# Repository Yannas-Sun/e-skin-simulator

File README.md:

# Modular e-Skin Network Simulator

This project is a lightweight software simulator for exploring scalable electronics in a modular, multi-layer electronic skin system. It is based on the planning work in `E_skin_plan_report.pdf`, which studies how an existing multi-modal e-skin platform can be redesigned into a compact, modular architecture with better data, power, and calibration scalability.

## Background

The simulated e-skin module follows the hardware structure described in the report:

- Hexagonal honeycomb-style module geometry
- Two internal `16 x 16` FSR force-sensing layers
- One `4 x 4` LIS3DH accelerometer layer
- Module-level sensing with patch-level aggregation
- Data throughput estimated from `560 channels/module` at a configurable sampling rate

The simulator is intended as an early design and communication tool rather than a high-fidelity finite-element or electronics model.

## Hardware Module Preview

The simulator is developed alongside a modular hardware prototype. Each hexagonal module is designed as a compact stack containing a local mainboard, a distributed accelerometer layer, and a folded FSR pressure-sensing array.

The same geometry supports patch-level assembly. The render below shows a five-module configuration that motivates the simulator's honeycomb workspace, patch grouping, and scalable data-throughput tools.

The complete PCB layouts, schematics, layer renders, and hardware development notes are maintained on the [`codex/hardware-prototype` branch](https://github.com/Yannas-Sun/e-skin-simulator/tree/codex/hardware-prototype).

## Embedded Firmware

The `firmware/` directory contains the current STM32G474 and Teensy 4.1 source,
Windows build/flash launchers, combined and standalone PC GUIs, and hardware
isolation tests for the physical module. The implemented prototype acquires two
16 x 16 FSR matrices and nine installed LIS2DH12 accelerometers. Start with
[`firmware/README.md`](firmware/README.md) for the current hardware status and
one-command programming workflow.

## Development Status

This project is still under active development. The current repository captures the first programmable simulation workflow, hardware-readout demo, and visualization interface. New functions will continue to be added, including richer scan strategies, external MCU-in-the-loop testing, event-driven sensing experiments, encoder/VAE-style data compression, and more complete multi-patch communication models.

## Features

### Module Network Dashboard

- Drag hexagonal e-skin modules into a honeycomb grid
- Assemble modules into arbitrary edge-aligned networks
- Box-select multiple modules or test objects
- Move, copy, paste, and delete selected items
- Combine selected modules into a patch
- Click a patch label or outline to focus the workspace view on that patch
- Show heatmap and throughput data for the focused patch until another item is selected
- Drag test objects onto the module network
- Choose object shape: circle, square, or triangle
- Adjust object size and mass
- Zoom the workspace using the mouse wheel, centered on the cursor
- Display a live pressure heatmap matching the assembled module topology
- Show module IDs on the heatmap
- Estimate real-time data throughput and Ethernet link use

### Programmable FSR Readout Demo

- Open an FSR readout demo showing DMUX row selection, 16 x 16 FSR voltage-divider readout, 16-channel ADC sampling, and four-wire SPI transfer back to the MCU
- Run the FSR demo from programmable Python virtual hardware classes rather than frontend-only formulas
- Simulate a MAX11632-style ADC command flow, including setup, averaging, reset, conversion input bytes, FIFO readout, EOC behavior, and 16-bit MISO output words
- Enter custom MOSI byte sequences from the web UI and inspect the resulting MISO FIFO output
- Generate the FSR heatmap from scanned ADC/FIFO data rather than directly from object placement
- Switch visualization behavior by refresh rate while keeping the same scan pipeline: MUX row scan followed by ADC FIFO column output
- Use the simulator as a bridge toward physical MCU testing, where an external MCU can later drive or validate the same command and data-transfer logic

### Programmable LIS3DH Accelerometer Demo

- Open an accelerometer demo showing a 4 x 4 LIS3DH array with shared SPI and individual chip-select control through a MUX
- Simulate LIS3DH SPI command encoding: `R/W`, multi-byte auto-increment, and 6-bit register address
- Read `OUT_X_L` through `OUT_Z_H` using the datasheet-style `0xE8` command byte
- Adjust the virtual object's vibration strength and footprint
- Decode X/Y/Z acceleration only from returned MISO register bytes
- Generate the hardware heatmap from decoded MISO data rather than direct object placement
- Display counted SPI traffic for address lines, SCK, MOSI, MISO, CS, and the upstream MCU-to-FPGA frame
- Solve the active-low LIS3DH chip-select electrical layer through ngspice when the solver is available

## Demo Videos

The repository includes two embedded demo previews to document the current simulator behavior. The original MP4 recordings are kept in `docs/demo/`, while the GIF previews below are used because GitHub README pages do not render repository-hosted MP4 files as inline players.

### Programmable FSR Readout Demo

Demonstrates the programmable FSR readout page, including MUX-controlled row scanning, ADC/FIFO-based column readout, MOSI command input, MISO output inspection, and hardware-derived heatmap generation.

### Module Network Dashboard

Demonstrates the modular e-skin dashboard, including honeycomb-style module placement, object interaction, patch-oriented pressure visualization, module identifiers, and data-throughput feedback.

These videos show the current state of the prototype. The simulator remains in progress, and future videos will be updated as new hardware models, external MCU workflows, scan strategies, and algorithm experiments are added.

## Running

This project uses only the Python standard library for the backend and plain HTML/CSS/JavaScript for the frontend.

```powershell
python server.py
```

Then open:

```text
http://127.0.0.1:8000
```

Use the HTTP address above rather than opening `index.html` directly, because the frontend calls the Python backend API at `/api/simulate`.

## ngspice Electrical Backend

The project includes an optional ngspice adapter for circuit-level simulation. The current deployment uses the official Windows 64-bit ngspice console executable and keeps the downloaded runtime under the ignored local `tools/ngspice/` directory.

The backend discovers ngspice in this order:

1. `NGSPICE_EXECUTABLE`
2. `tools/ngspice/Spice64/bin/ngspice_con.exe`
3. `ngspice_con` or `ngspice` on `PATH`

The health endpoint runs a `3.3 V` FSR voltage-divider smoke test through ngspice:

```text
http://127.0.0.1:8000/api/ngspice-health
```

The interactive FSR demo now uses ngspice for the selected-row electrical network. For each scanned row, Python computes the current FSR resistance values, ngspice solves the row source, MUX on-resistance, 16 FSRs, and 16 load resistors, then the Python MAX11632 model converts those node voltages into FIFO and MISO words.

The accelerometer demo uses ngspice for the LIS3DH active-low chip-select electrical layer. The address decoder network is solved as 16 nCS lines with pull-ups, LIS3DH input leakage, and one selected decoder sink. Python then continues with the digital LIS3DH register/SPI behavior. The dashboard-level module heatmap still uses the fast Python pressure model.

## Fusion 3D Model Preview

The dashboard includes a load-on-demand Fusion OBJ preview for the module model. The large `Module.obj` asset is tracked with Git LFS through `.gitattributes`, while the viewer uses a small vendored Three.js subset so the preview works without a CDN.

## Basic Usage

1. Drag an `e-Skin Module` from the right panel into the workspace.
2. Arrange modules on the honeycomb grid.
3. Drag a test object into the workspace.
4. Adjust object size, mass, and sampling rate from the right panel.
5. Read the pressure heatmap and data throughput from the left panel.
6. Drag on empty workspace space to box-select multiple items.
7. Use toolbar buttons or shortcuts:
   - `Copy`
   - `Paste`
   - `Delete`
   - `Ctrl+C`
   - `Ctrl+V`
   - `Delete` / `Backspace`
8. Click `FSR Demo` to inspect the hardware readout path for one 16 x 16 FSR layer.
9. Click `Accel Demo` to inspect the LIS3DH accelerometer-array readout path.

## Project Structure

```text
software-simulation/
  server.py                    # root launcher; keeps `python server.py` working
  backend/
    README.md                  # backend package map and API summary
    server.py                  # Python HTTP server and simulation API
    accel/
      README.md                # LIS3DH hardware model documentation
      hardware.py              # virtual LIS3DH, CS MUX, ngspice nCS drive, and SPI primitives
      sampler.py               # programmable LIS3DH scan controller
    electrical/
      README.md                # shared electrical solver documentation
      ngspice_backend.py       # optional circuit-level ngspice adapter and health check
    fsr/
      README.md                # FSR hardware model documentation
      hardware.py              # virtual DMUX, ADC, resistor, FSR, and FSR array primitives
      sampler.py               # programmable FSR scan controller
  circuits/
    ngspice/
      accel-cs-mux.cir         # LIS3DH active-low nCS pull-up/decoder-sink reference circuit
      fsr-divider.cir          # standalone FSR voltage-divider smoke-test circuit
      fsr-selected-row.cir     # selected-row FSR network with MUX on-resistance and 16 load dividers
  frontend/
    assets/
      models/                 # Fusion OBJ/MTL module preview assets
    accelerometer-demo.html    # LIS3DH accelerometer-array readout demo
    index.html                 # module-network dashboard
    fsr-demo.html              # FSR readout circuit demo
    styles.css                 # shared UI styling
    vendor/
      three/                   # vendored Three.js modules used by the OBJ viewer
    js/
      app.js                   # dashboard interaction, rendering, and API calls
      accelerometer-demo.js    # LIS3DH visualization and MISO-driven heatmap logic
      fsr-demo.js              # FSR visualization and MISO-driven heatmap logic
      module-3d-viewer.js      # dashboard Fusion OBJ preview viewer
  docs/
    datasheets/                # component datasheets used by the virtual hardware models
    demo/
      demo1.mp4                # dashboard workflow demo
      demo2.mp4                # programmable FSR readout demo
    hardware/                  # module and patch renders used by this README
    references/                # project reports and source PDFs
  firmware/                    # STM32/Teensy firmware, tests, commands, and PC GUIs
  CHANGELOG.md                 # ordered record of pushed changes
```

Local KiCad prototypes and downloaded helper tools can live beside the simulator under `prototype/` and `tools/`. They are intentionally excluded from software pushes so the repository stays focused on the runnable simulation platform.

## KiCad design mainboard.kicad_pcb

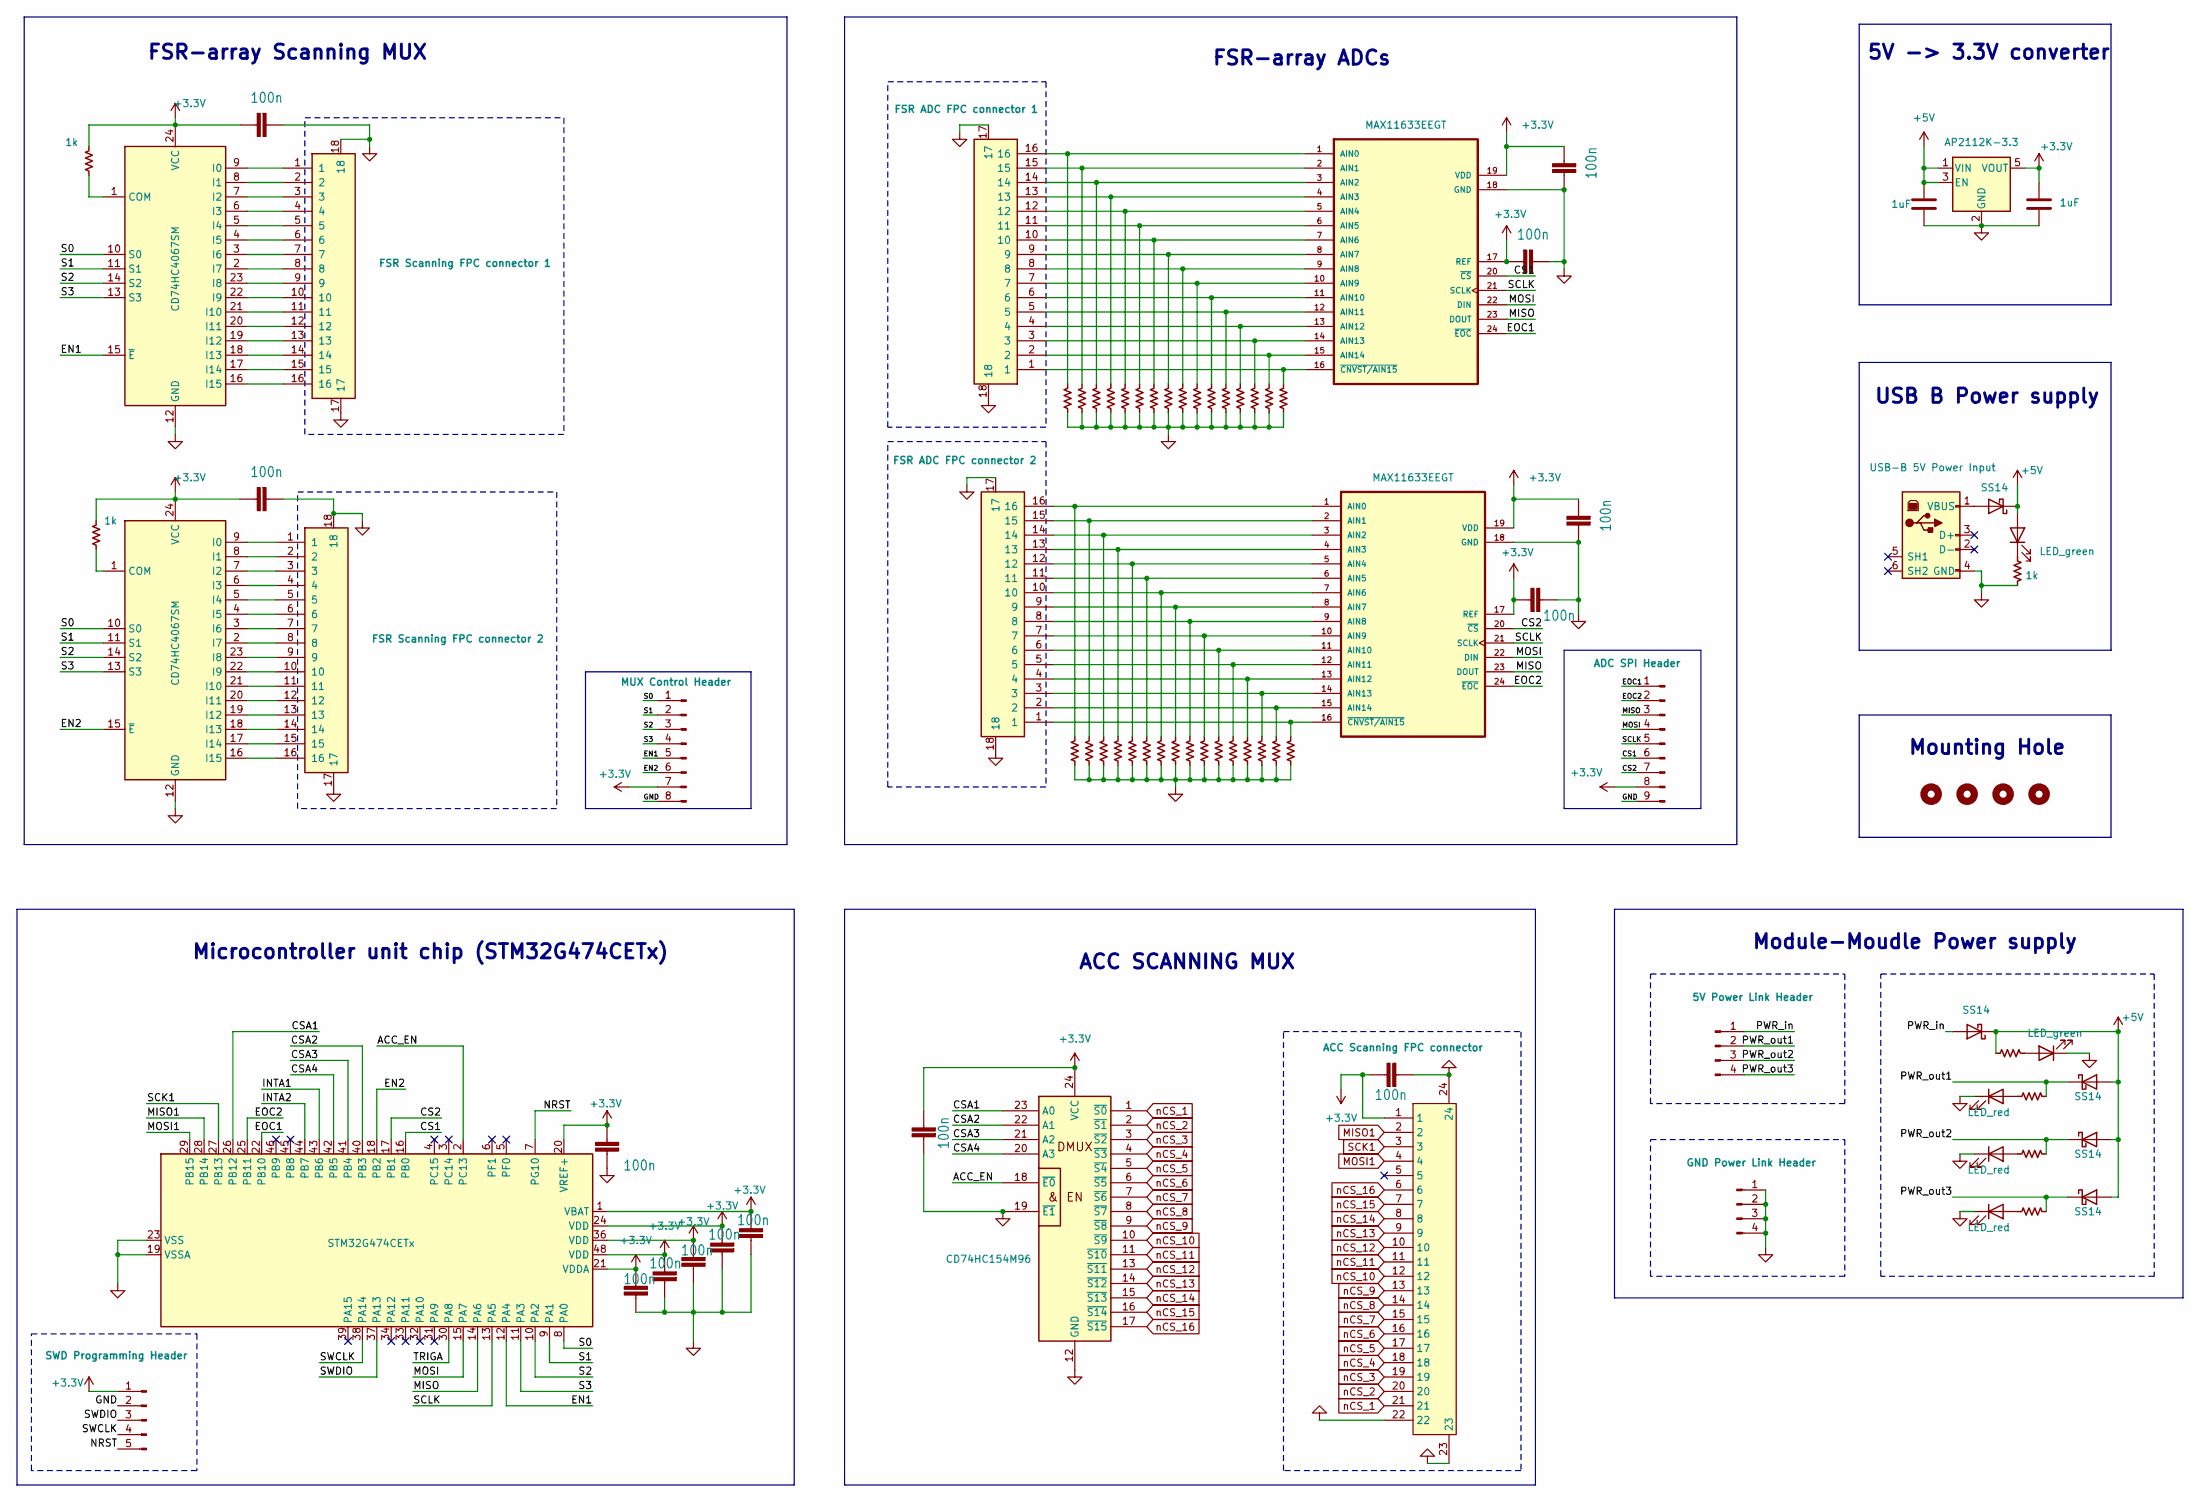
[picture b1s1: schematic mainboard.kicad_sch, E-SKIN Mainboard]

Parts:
ACC_DEC1: CD74HC154M96; SOIC127P1030X265-24N
ACC_FPC1: ACC Scanning FPC connector; AFC01-S22FCA-00; LCSC Part C262668
ADC_SPI_HDR1: ADC SPI Header; PinHeader_1x09_P2.54mm_Vertical
C1, C2, C5, C6, C7, C8, C9, C10, C11, C12, C13, C14, C15, C16: 100n; C0603
C3, C4: 1uF; C0603
COL_ADC1, COL_ADC2: MAX11633EEGT
COL_FPC1: FSR ADC FPC connector 1; AFC01-S16FCA-00
COL_FPC2: FSR ADC FPC connector 2; AFC01-S16FCA-00
D1, D6: LED_green; LED_0603_1608Metric
D2, D3, D4, D5, D10: SS14; D_SMA
D7, D8, D9: LED_red; LED_0603_1608Metric
LDO_3V3: AP2112K-3.3; SOT-23-5
MCU1: STM32G474CETx; LQFP-48_7x7mm_P0.5mm
MOUNT2, MOUNT3, MOUNT4, MOUNT5: M3 Mounting Hole; MountingHole_3.2mm_M3
MUX_CTRL_HDR1: MUX Control Header; PinHeader_1x08_P2.54mm_Vertical
PWR_5V_LINK1: 5V Power Link Header; PinHeader_1x04_P2.54mm_Horizontal
PWR_GND_LINK1: GND Power Link Header; PinHeader_1x04_P2.54mm_Horizontal
ROW_FPC1: FSR Scanning FPC connector 1; AFC01-S16FCA-00
ROW_FPC2: FSR Scanning FPC connector 2; AFC01-S16FCA-00
ROW_MUX1, ROW_MUX2: CD74HC4067SM; SSOP-24_5.3x8.2mm_P0.65mm
R_ADC1_01, R_ADC1_02, R_ADC1_03, R_ADC1_04, R_ADC1_05, R_ADC1_06, R_ADC1_07, R_ADC1_08, R_ADC1_09, R_ADC1_10, R_ADC1_11, R_ADC1_12, R_ADC1_13, R_ADC1_14, R_ADC1_15, R_ADC1_16, R_ADC2_01, R_ADC2_02, R_ADC2_03, R_ADC2_04, R_ADC2_05, R_ADC2_06, R_ADC2_07, R_ADC2_08, R_ADC2_09, R_ADC2_10, R_ADC2_11, R_ADC2_12, R_ADC2_13, R_ADC2_14, R_ADC2_15, R_ADC2_16: 10k; R_0603_1608Metric
R_LED_PWR1, R_LED_PWR2, R_LED_PWR3, R_LED_PWR4: 1k; R_0603_1608Metric
R_LED_USB1: 1k; R_0603_1608Metric
R_MUX1_COM1, R_MUX2_COM1: 1k; R_0603_1608Metric
SWD_HDR1: SWD Programming Header; PinHeader_1x05_P2.54mm_Vertical
USB_PWR_IN1: USB-B 5V Power Input; SS52300001; Mouser Part Number 530-SS-52300-001

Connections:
+3.3V: ACC_DEC1.24 (VCC), ACC_FPC1.1, ADC_SPI_HDR1.8, C1.2, C2.1, C3.1, C5.2, C6.2, C7.2, C8.1, C9.2, C10.2, C11.2, C12.2, C13.2, C14.2, C15.2, C16.2, COL_ADC1.17 (REF), COL_ADC1.19 (VDD), COL_ADC2.17 (REF), COL_ADC2.19 (VDD), LDO_3V3.5 (VOUT), MCU1.1 (VBAT), MCU1.20 (VREF+), MCU1.21 (VDDA), MCU1.24 (VDD), MCU1.36 (VDD), MCU1.48 (VDD), MUX_CTRL_HDR1.7, ROW_MUX1.24 (VCC), ROW_MUX2.24 (VCC), R_MUX1_COM1.1, R_MUX2_COM1.1, SWD_HDR1.1; also elsewhere on the board
+5V: C4.1, D1.2 (A), D2.1 (K), D3.2 (A), D4.2 (A), D5.2 (A), D10.1 (K), LDO_3V3.1 (VIN), LDO_3V3.3 (EN), R_LED_PWR1.2
/ACC_EN: ACC_DEC1.18 (~E0), MCU1.2 (PC13); also elsewhere on the board
/CS1: ADC_SPI_HDR1.6, COL_ADC1.20 (~CS), MCU1.16 (PB0)
/CS2: ADC_SPI_HDR1.7, COL_ADC2.20 (~CS), MCU1.17 (PB1)
/CSA1: ACC_DEC1.23 (A0), MCU1.26 (PB12); also elsewhere on the board
/CSA2: ACC_DEC1.22 (A1), MCU1.40 (PB3); also elsewhere on the board
/CSA3: ACC_DEC1.21 (A2), MCU1.41 (PB4); also elsewhere on the board
/CSA4: ACC_DEC1.20 (A3), MCU1.42 (PB5); also elsewhere on the board
/EN1: MCU1.12 (PA4), MUX_CTRL_HDR1.5, ROW_MUX1.15 (~E)
/EN2: MCU1.18 (PB2), MUX_CTRL_HDR1.6, ROW_MUX2.15 (~E)
/EOC1: ADC_SPI_HDR1.1, COL_ADC1.24 (~EOC), MCU1.22 (PB10)
/EOC2: ADC_SPI_HDR1.2, COL_ADC2.24 (~EOC), MCU1.25 (PB11)
/INTA1: MCU1.43 (PB6)
/INTA2: MCU1.44 (PB7)
/MISO: ADC_SPI_HDR1.3, COL_ADC1.23 (DOUT), COL_ADC2.23 (DOUT), MCU1.14 (PA6)
/MOSI: ADC_SPI_HDR1.4, COL_ADC1.22 (DIN), COL_ADC2.22 (DIN), MCU1.15 (PA7)
/NRST: MCU1.7 (PG10), SWD_HDR1.5
/PWR_in: D2.2 (A), PWR_5V_LINK1.1
/PWR_out1: D3.1 (K), PWR_5V_LINK1.2, R_LED_PWR2.1
/PWR_out2: D4.1 (K), PWR_5V_LINK1.3, R_LED_PWR3.1
/PWR_out3: D5.1 (K), PWR_5V_LINK1.4, R_LED_PWR4.1
/S0: MCU1.8 (PA0), MUX_CTRL_HDR1.1, ROW_MUX1.10 (S0), ROW_MUX2.10 (S0)
/S1: MCU1.9 (PA1), MUX_CTRL_HDR1.2, ROW_MUX1.11 (S1), ROW_MUX2.11 (S1)
/S2: MCU1.10 (PA2), MUX_CTRL_HDR1.3, ROW_MUX1.14 (S2), ROW_MUX2.14 (S2)
/S3: MCU1.11 (PA3), MUX_CTRL_HDR1.4, ROW_MUX1.13 (S3), ROW_MUX2.13 (S3)
/SCLK: ADC_SPI_HDR1.5, COL_ADC1.21 (SCLK), COL_ADC2.21 (SCLK), MCU1.13 (PA5)
/SWCLK: MCU1.38 (PA14), SWD_HDR1.4
/SWDIO: MCU1.37 (PA13), SWD_HDR1.3
/TRIGA: MCU1.30 (PA8)
GND: ACC_DEC1.12 (GND), ACC_DEC1.19 (~E1), ACC_FPC1.22, ACC_FPC1.23, ACC_FPC1.24, ADC_SPI_HDR1.9, C1.1, C2.2, C3.2, C4.2, C5.1, C6.1, C7.1, C8.2, C9.1, C10.1, C11.1, C12.1, C13.1, C14.1, C15.1, C16.1, COL_ADC1.18 (GND), COL_ADC2.18 (GND), COL_FPC1.17, COL_FPC1.18, COL_FPC2.17, COL_FPC2.18, D6.1 (K), D7.1 (K), D8.1 (K), D9.1 (K), LDO_3V3.2 (GND), MCU1.19 (VSSA), MCU1.23 (VSS), MCU1.35 (VSS), MCU1.47 (VSS), MUX_CTRL_HDR1.8, PWR_GND_LINK1.1, PWR_GND_LINK1.2, PWR_GND_LINK1.3, PWR_GND_LINK1.4, ROW_FPC1.17, ROW_FPC1.18, ROW_FPC2.17, ROW_FPC2.18, ROW_MUX1.12 (GND), ROW_MUX2.12 (GND), R_ADC1_01.2, R_ADC1_02.2, R_ADC1_03.2, R_ADC1_04.2, R_ADC1_05.2, R_ADC1_06.2, R_ADC1_07.2, R_ADC1_08.2, R_ADC1_09.2, R_ADC1_10.2, R_ADC1_11.2, R_ADC1_12.2, R_ADC1_13.2, R_ADC1_14.2, R_ADC1_15.2, R_ADC1_16.2, R_ADC2_01.2, R_ADC2_02.2, R_ADC2_03.2, R_ADC2_04.2, R_ADC2_05.2, R_ADC2_06.2, R_ADC2_07.2, R_ADC2_08.2, R_ADC2_09.2, R_ADC2_10.2, R_ADC2_11.2, R_ADC2_12.2, R_ADC2_13.2, R_ADC2_14.2, R_ADC2_15.2, R_ADC2_16.2, R_LED_USB1.1, SWD_HDR1.2, USB_PWR_IN1.4 (GND); also elsewhere on the board
MISO1: ACC_FPC1.2, MCU1.28 (PB14)
MOSI1: ACC_FPC1.4, MCU1.29 (PB15)
unnamed: COL_ADC1.1 (AIN0), COL_FPC1.16, R_ADC1_01.1
unnamed: COL_ADC1.2 (AIN1), COL_FPC1.15, R_ADC1_02.1
unnamed: COL_ADC1.3 (AIN2), COL_FPC1.14, R_ADC1_03.1
unnamed: COL_ADC1.4 (AIN3), COL_FPC1.13, R_ADC1_04.1
unnamed: COL_ADC1.5 (AIN4), COL_FPC1.12, R_ADC1_05.1
unnamed: COL_ADC1.6 (AIN5), COL_FPC1.11, R_ADC1_06.1
unnamed: COL_ADC1.7 (AIN6), COL_FPC1.10, R_ADC1_07.1
unnamed: COL_ADC1.8 (AIN7), COL_FPC1.9, R_ADC1_08.1
unnamed: COL_ADC1.9 (AIN8), COL_FPC1.8, R_ADC1_09.1
unnamed: COL_ADC1.10 (AIN9), COL_FPC1.7, R_ADC1_10.1
unnamed: COL_ADC1.11 (AIN10), COL_FPC1.6, R_ADC1_11.1
unnamed: COL_ADC1.12 (AIN11), COL_FPC1.5, R_ADC1_12.1
unnamed: COL_ADC1.13 (AIN12), COL_FPC1.4, R_ADC1_13.1
unnamed: COL_ADC1.14 (AIN13), COL_FPC1.3, R_ADC1_14.1
unnamed: COL_ADC1.15 (AIN14), COL_FPC1.2, R_ADC1_15.1
unnamed: COL_ADC1.16 (~CNVST/AIN15), COL_FPC1.1, R_ADC1_16.1
unnamed: COL_ADC2.1 (AIN0), COL_FPC2.16, R_ADC2_01.1
unnamed: COL_ADC2.2 (AIN1), COL_FPC2.15, R_ADC2_02.1
unnamed: COL_ADC2.3 (AIN2), COL_FPC2.14, R_ADC2_03.1
unnamed: COL_ADC2.4 (AIN3), COL_FPC2.13, R_ADC2_04.1
unnamed: COL_ADC2.5 (AIN4), COL_FPC2.12, R_ADC2_05.1
unnamed: COL_ADC2.6 (AIN5), COL_FPC2.11, R_ADC2_06.1
unnamed: COL_ADC2.7 (AIN6), COL_FPC2.10, R_ADC2_07.1
unnamed: COL_ADC2.8 (AIN7), COL_FPC2.9, R_ADC2_08.1
unnamed: COL_ADC2.9 (AIN8), COL_FPC2.8, R_ADC2_09.1
unnamed: COL_ADC2.10 (AIN9), COL_FPC2.7, R_ADC2_10.1
unnamed: COL_ADC2.11 (AIN10), COL_FPC2.6, R_ADC2_11.1
unnamed: COL_ADC2.12 (AIN11), COL_FPC2.5, R_ADC2_12.1
unnamed: COL_ADC2.13 (AIN12), COL_FPC2.4, R_ADC2_13.1
unnamed: COL_ADC2.14 (AIN13), COL_FPC2.3, R_ADC2_14.1
unnamed: COL_ADC2.15 (AIN14), COL_FPC2.2, R_ADC2_15.1
unnamed: COL_ADC2.16 (~CNVST/AIN15), COL_FPC2.1, R_ADC2_16.1
unnamed: D1.1 (K), R_LED_USB1.2
unnamed: D6.2 (A), R_LED_PWR1.1
unnamed: D7.2 (A), R_LED_PWR2.2
unnamed: D8.2 (A), R_LED_PWR3.2
unnamed: D9.2 (A), R_LED_PWR4.2
unnamed: D10.2 (A), USB_PWR_IN1.1 (VBUS)
unnamed: ROW_MUX1.1 (COM), R_MUX1_COM1.2
unnamed: ROW_FPC1.1, ROW_MUX1.9 (I0)
unnamed: ROW_FPC1.2, ROW_MUX1.8 (I1)
unnamed: ROW_FPC1.3, ROW_MUX1.7 (I2)
unnamed: ROW_FPC1.4, ROW_MUX1.6 (I3)
unnamed: ROW_FPC1.5, ROW_MUX1.5 (I4)
unnamed: ROW_FPC1.6, ROW_MUX1.4 (I5)
unnamed: ROW_FPC1.7, ROW_MUX1.3 (I6)
unnamed: ROW_FPC1.8, ROW_MUX1.2 (I7)
unnamed: ROW_FPC1.9, ROW_MUX1.23 (I8)
unnamed: ROW_FPC1.10, ROW_MUX1.22 (I9)
unnamed: ROW_FPC1.11, ROW_MUX1.21 (I10)
unnamed: ROW_FPC1.12, ROW_MUX1.20 (I11)
unnamed: ROW_FPC1.13, ROW_MUX1.19 (I12)
unnamed: ROW_FPC1.14, ROW_MUX1.18 (I13)
unnamed: ROW_FPC1.15, ROW_MUX1.17 (I14)
unnamed: ROW_FPC1.16, ROW_MUX1.16 (I15)
unnamed: ROW_MUX2.1 (COM), R_MUX2_COM1.2
unnamed: ROW_FPC2.1, ROW_MUX2.9 (I0)
unnamed: ROW_FPC2.2, ROW_MUX2.8 (I1)
unnamed: ROW_FPC2.3, ROW_MUX2.7 (I2)
unnamed: ROW_FPC2.4, ROW_MUX2.6 (I3)
unnamed: ROW_FPC2.5, ROW_MUX2.5 (I4)
unnamed: ROW_FPC2.6, ROW_MUX2.4 (I5)
unnamed: ROW_FPC2.7, ROW_MUX2.3 (I6)
unnamed: ROW_FPC2.8, ROW_MUX2.2 (I7)
unnamed: ROW_FPC2.9, ROW_MUX2.23 (I8)
unnamed: ROW_FPC2.10, ROW_MUX2.22 (I9)
unnamed: ROW_FPC2.11, ROW_MUX2.21 (I10)
unnamed: ROW_FPC2.12, ROW_MUX2.20 (I11)
unnamed: ROW_FPC2.13, ROW_MUX2.19 (I12)
unnamed: ROW_FPC2.14, ROW_MUX2.18 (I13)
unnamed: ROW_FPC2.15, ROW_MUX2.17 (I14)
unnamed: ROW_FPC2.16, ROW_MUX2.16 (I15)
SCK1: ACC_FPC1.3, MCU1.27 (PB13)
nCS_1: ACC_DEC1.1 (~S0), ACC_FPC1.21; also elsewhere on the board
nCS_2: ACC_DEC1.2 (~S1), ACC_FPC1.20; also elsewhere on the board
nCS_3: ACC_DEC1.3 (~S2), ACC_FPC1.19; also elsewhere on the board
nCS_4: ACC_DEC1.4 (~S3), ACC_FPC1.18; also elsewhere on the board
nCS_5: ACC_DEC1.5 (~S4), ACC_FPC1.17; also elsewhere on the board
nCS_6: ACC_DEC1.6 (~S5), ACC_FPC1.16; also elsewhere on the board
nCS_7: ACC_DEC1.7 (~S6), ACC_FPC1.15; also elsewhere on the board
nCS_8: ACC_DEC1.8 (~S7), ACC_FPC1.14; also elsewhere on the board
nCS_9: ACC_DEC1.9 (~S8), ACC_FPC1.13; also elsewhere on the board
nCS_10: ACC_DEC1.10 (~S9), ACC_FPC1.12; also elsewhere on the board
nCS_11: ACC_DEC1.11 (~S10), ACC_FPC1.11; also elsewhere on the board
nCS_12: ACC_DEC1.13 (~S11), ACC_FPC1.10; also elsewhere on the board
nCS_13: ACC_DEC1.14 (~S12), ACC_FPC1.9; also elsewhere on the board
nCS_14: ACC_DEC1.15 (~S13), ACC_FPC1.8; also elsewhere on the board
nCS_15: ACC_DEC1.16 (~S14), ACC_FPC1.7; also elsewhere on the board
nCS_16: ACC_DEC1.17 (~S15), ACC_FPC1.6; also elsewhere on the board

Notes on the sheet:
FSR-array ADCs
USB B Power supply
5V -> 3.3V converter
ACC SCANNING MUX
Microcontroller unit chip (STM32G474CETx)
FSR-array Scanning MUX
Mounting Hole
Module-Moudle Power supply

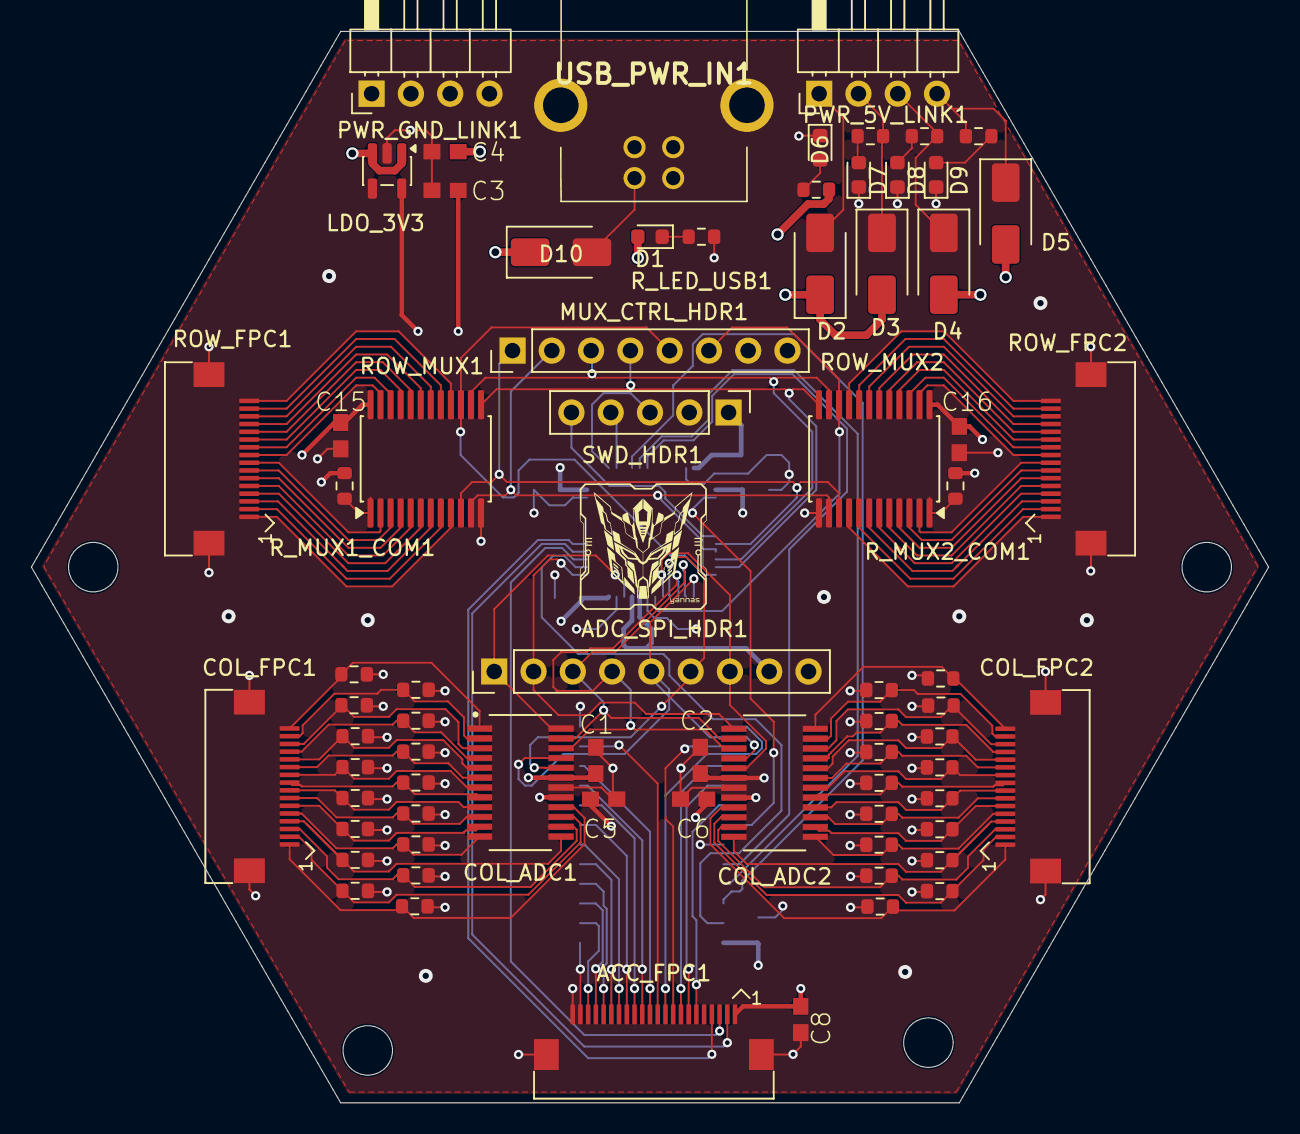
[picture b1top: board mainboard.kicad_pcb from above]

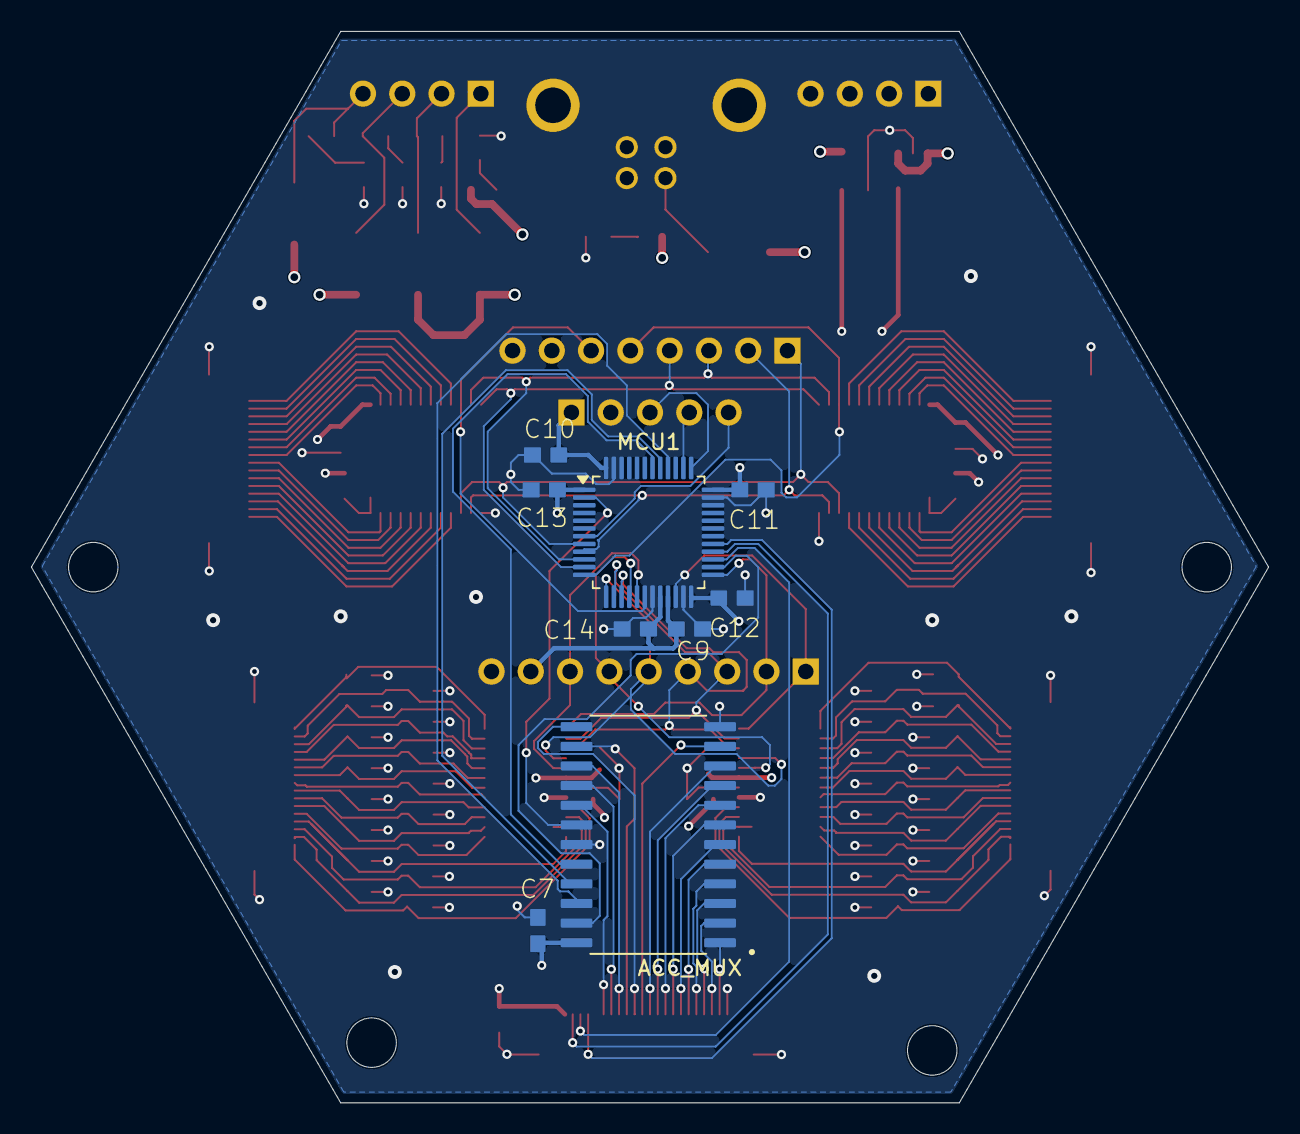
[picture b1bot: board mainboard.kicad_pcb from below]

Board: 4 copper layers, 80.0 x 69.3 mm, 89 parts (9 on the bottom side), 119 nets.

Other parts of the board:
ACC_MUX: CD74HC154M96; SOIC127P1030X265-24N
IC: LOGO; IC_LOGO
LOGO: LOGO

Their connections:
+3.3V: ACC_MUX.24 (VCC); also elsewhere on the board
/ACC_EN: ACC_MUX.18 (~E0); also elsewhere on the board
/CSA1: ACC_MUX.23 (A0); also elsewhere on the board
/CSA2: ACC_MUX.22 (A1); also elsewhere on the board
/CSA3: ACC_MUX.21 (A2); also elsewhere on the board
/CSA4: ACC_MUX.20 (A3); also elsewhere on the board
GND: ACC_MUX.12 (GND), ACC_MUX.19 (~E1); also elsewhere on the board
nCS_1: ACC_MUX.1 (~S0); also elsewhere on the board
nCS_2: ACC_MUX.2 (~S1); also elsewhere on the board
nCS_3: ACC_MUX.3 (~S2); also elsewhere on the board
nCS_4: ACC_MUX.4 (~S3); also elsewhere on the board
nCS_5: ACC_MUX.5 (~S4); also elsewhere on the board
nCS_6: ACC_MUX.6 (~S5); also elsewhere on the board
nCS_7: ACC_MUX.7 (~S6); also elsewhere on the board
nCS_8: ACC_MUX.8 (~S7); also elsewhere on the board
nCS_9: ACC_MUX.9 (~S8); also elsewhere on the board
nCS_10: ACC_MUX.10 (~S9); also elsewhere on the board
nCS_11: ACC_MUX.11 (~S10); also elsewhere on the board
nCS_12: ACC_MUX.13 (~S11); also elsewhere on the board
nCS_13: ACC_MUX.14 (~S12); also elsewhere on the board
nCS_14: ACC_MUX.15 (~S13); also elsewhere on the board
nCS_15: ACC_MUX.16 (~S14); also elsewhere on the board
nCS_16: ACC_MUX.17 (~S15); also elsewhere on the board

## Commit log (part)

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2026-05-12 Initial e-skin simulator
2026-05-12 Add patch grouping and focus mode
2026-05-12 Add FSR readout circuit demo
2026-05-12 Improve FSR demo circuit layout
2026-05-12 Correct FSR readout circuit logic
2026-05-12 Make FSR readout programmable in Python
2026-05-12 Simplify FSR buses and model SPI lines
2026-05-12 Clean up FSR circuit view and changelog types
2026-05-12 Prevent module overlap and show FSR clock IO
2026-05-12 Add FSR pressure object scan
2026-05-12 Add FSR object mass controls and binary SPI trace
2026-05-12 Render square FSR object coverage
2026-05-12 Align FSR object footprint controls
2026-05-12 Drive FSR display from hardware heatmap
2026-05-12 Update FSR heatmap from MISO frames
2026-05-12 Keep FSR heatmap until MISO refresh
2026-05-13 Organize project folder structure
2026-05-14 Model ADC FIFO scan command sequence
2026-05-14 Animate SPI phases with hardware clock
2026-05-14 Make FSR visual phase changes visible
2026-05-14 Show scan line throughput rates
2026-05-14 Report MCU-counted scan line rates
2026-05-14 Restore scanned-only FSR highlighting
2026-05-14 Soften FSR heatmap gradient
2026-05-14 Drive SPI highlighting from line state
2026-05-14 Add scan waveform visualization
2026-05-14 Add rolling transfer waveforms
2026-05-14 Drive waveforms from hardware timing
2026-05-14 Stabilize clock waveform rendering
2026-05-14 Remove live waveform display
2026-05-15 Add STM32G474 uplink SPI simulation
2026-05-15 Tighten FSR load resistor drawing
2026-05-15 Align ADC simulation with MAX11632 protocol
2026-05-15 Add MAX11632 input byte model
2026-05-15 Match ADC DOUT format and widen readout panel
2026-05-15 Add manual ADC MOSI simulator
2026-05-15 Add FIFO column scan animation
2026-05-15 Fix FIFO playback reset at high refresh
2026-05-15 Add frequency-aware scan display modes
2026-05-15 Correct full-frame refresh visualization
2026-05-15 Hide MUX scan in high-frequency mode
2026-05-15 Unify scan pipeline across visualization modes
2026-05-18 Add demo videos and usage documentation
2026-05-18 Show demo videos on homepage
2026-05-18 Embed demo videos in GitHub README
2026-05-18 Show README demo previews as GIFs
2026-05-18 Refresh dashboard demo preview
    # Conflicts:
    # demo/demo1-preview.gif
2026-05-18 Refresh FSR readout demo preview
2026-05-18 Normalize README demo preview layout
2026-05-19 Update prototype schematic for STM32G474 MCU
2026-05-19 Connect STM32G474CETx in prototype schematic
2026-05-19 Add CD74HC4067 datasheet to hardware branch
2026-05-19 Move prototype hardware to dedicated branch
2026-05-19 Add updated hardware prototype files
2026-05-19 Make hardware PCB layout symmetric
2026-05-19 Compact hardware PCB to 80mm symmetric layout
2026-05-19 Fix compact PCB edge cuts
2026-05-19 Add initial symmetric PCB routing
2026-05-20 Add LIS3DH accelerometer demo
2026-05-23 Update mainboard hardware prototype
2026-05-23 Adjust mainboard PCB symmetry
2026-05-23 Add address-stepped accelerometer scan animation
2026-05-23 Fix accelerometer demo layout and dragging
2026-05-24 Sync current mainboard hardware
2026-05-25 Publish mainboard 2.0 routed PCB snapshot
2026-05-25 Add hardware README and schematic documentation
2026-05-25 Refine hardware README power documentation
2026-05-25 Update hardware README schematic preview
2026-05-25 Update hardware README development status
2026-06-01 Add current modular e-skin hardware prototypes
    [Hardware] Add the complete prototype/new hardware workspace without local backups. Include the routed mainboard revisions, ACC layer design, folded FSR-array design, project-local symbol and footpri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
2026-06-01 Update modular e-skin project homepage
    Place the complete module and multi-module renders at the top of the repository homepage. Add layered documentation for the mainboard, ACC layer, and folded FSR array with PCB renders, schematics, re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
2026-06-01 Fix mainboard render link
    Update the Mainboard 2.0 documentation to reference the tracked Rendering.png asset instead of the obsolete rendergraph.png filename.
2026-06-01 Add hardware renders to software homepage
    Introduce the modular hardware prototype on the software-simulator README with a stacked module render, a five-module patch demo render, a short explanation of how the geometry informs the simulator,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
2026-06-02 Organize software repository layout
2026-06-02 Deploy optional ngspice electrical backend
2026-06-02 Make dashboard grid snapping permanent
2026-06-03 Connect ngspice to FSR readout path
2026-06-03 Add dashboard Fusion 3D model preview
2026-06-03 Document FSR hardware classes
2026-06-03 Add rendered FSR hardware documentation page
2026-06-03 Revert "Add rendered FSR hardware documentation page"
    This reverts commit 6fd1d67173480a861605d4c6ed66bf74dc9f8a7d.
2026-06-03 Add ngspice ACC drive and backend subpackages
2026-06-03 Rename hardware branch and keep prototype new
2026-06-03 Restructure hardware branch homepage
